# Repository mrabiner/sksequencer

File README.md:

# sksequencer
Kondo RF Sequencer

## Function
This board is a TX/RX sequencer for an amateur-radio station. An ATmega328P monitors the PTT line from the radio. When PTT is keyed (pulled to ground), the firmware switches the station in a set order: it removes power from the mast-mounted LNA, switches the coax relays and then enables the power amplifier. When PTT is released, it runs the same steps in reverse. This keeps RF out of the LNA and keeps the relays from switching while RF is present (no hot-switching). The sequence timing is set by the firmware.

## Inputs / Outputs

| Pad | Name | Type | Description |
|-----|------|------|-------------|
| TP13 | 5V PAD | Power in | +5 V logic supply. Protected by F1 (0.5 A polyfuse), Q7 (reverse-polarity P-FET) and D6 (6.8 V TVS) |
| TP15 | V1 | Power in | +15 V LNA supply, switched to the LNA output |
| TP16 | V2 | Power in | +28 V coax-relay supply, switched to the RELAY output |
| TP12 | PTT | Input | PTT from the radio, active low. 10k pull-up to +5 V, 1k series resistor and 100 nF filter cap, to PD2 |
| TP8 | LNA | Output | High-side switched +15 V (Q5 BS250P driven by Q1), with flyback diode |
| TP9 | RELAY | Output | High-side switched +28 V (Q6 BS250P driven by Q2), with flyback diode |
| TP10 | AMP | Output | Low-side open-drain output (Q3 BS170) for amplifier keying, clamped by a 36 V TVS |
| TP11 | OUT#4 | Output | Low-side open-drain output (Q4 BS170), spare, clamped by a 36 V TVS |
| TP14, TP17–TP21 | GND | Ground | Ground pads |

### Headers
| Ref | Description |
|-----|-------------|
| J1 | 1x4, output drive signals PD5, PD6, PD7, PB0 (MCU side of the gate resistors) |
| J2 | 1x6, RESET, PD0/RXD, PD1/TXD, PD2 (PTT), PD3, PD4 |
| J3 | 1x14, PC0–PC5, GND, AREF, +5 V, PB5–PB1 (spare I/O) |
| J4 | 2x3 AVR ISP programming header |
| SW1 | Reset pushbutton |

The MCU runs from a 16 MHz crystal (Y1). D1 is a +5 V power indicator LED.

## Project Files

| File | Description |
|------|-------------|
| `sequencer.kicad_pro` | KiCad project file |
| `sequencer.kicad_sch` | Schematic |
| `sequencer.kicad_pcb` | PCB layout |
| `sequencer.kicad_sym` | Project symbol library (BS250P and others) |
| `ECS-160-18-4X-CKM.kicad_sym` | Symbol for the 16 MHz crystal Y1 |
| `sym-lib-table` | Project symbol library table |
| `fp-lib-table` | Project footprint library table |
| `.gitignore` | Leaves KiCad backups, history, `.kicad_prl` user settings and generated output out of git |

**Note:** `fp-lib-table` references `sequencer footprint library.pretty` (footprints for Y1, Q5 and Q6), which is not yet in the repository.

Created with KiCad 10.

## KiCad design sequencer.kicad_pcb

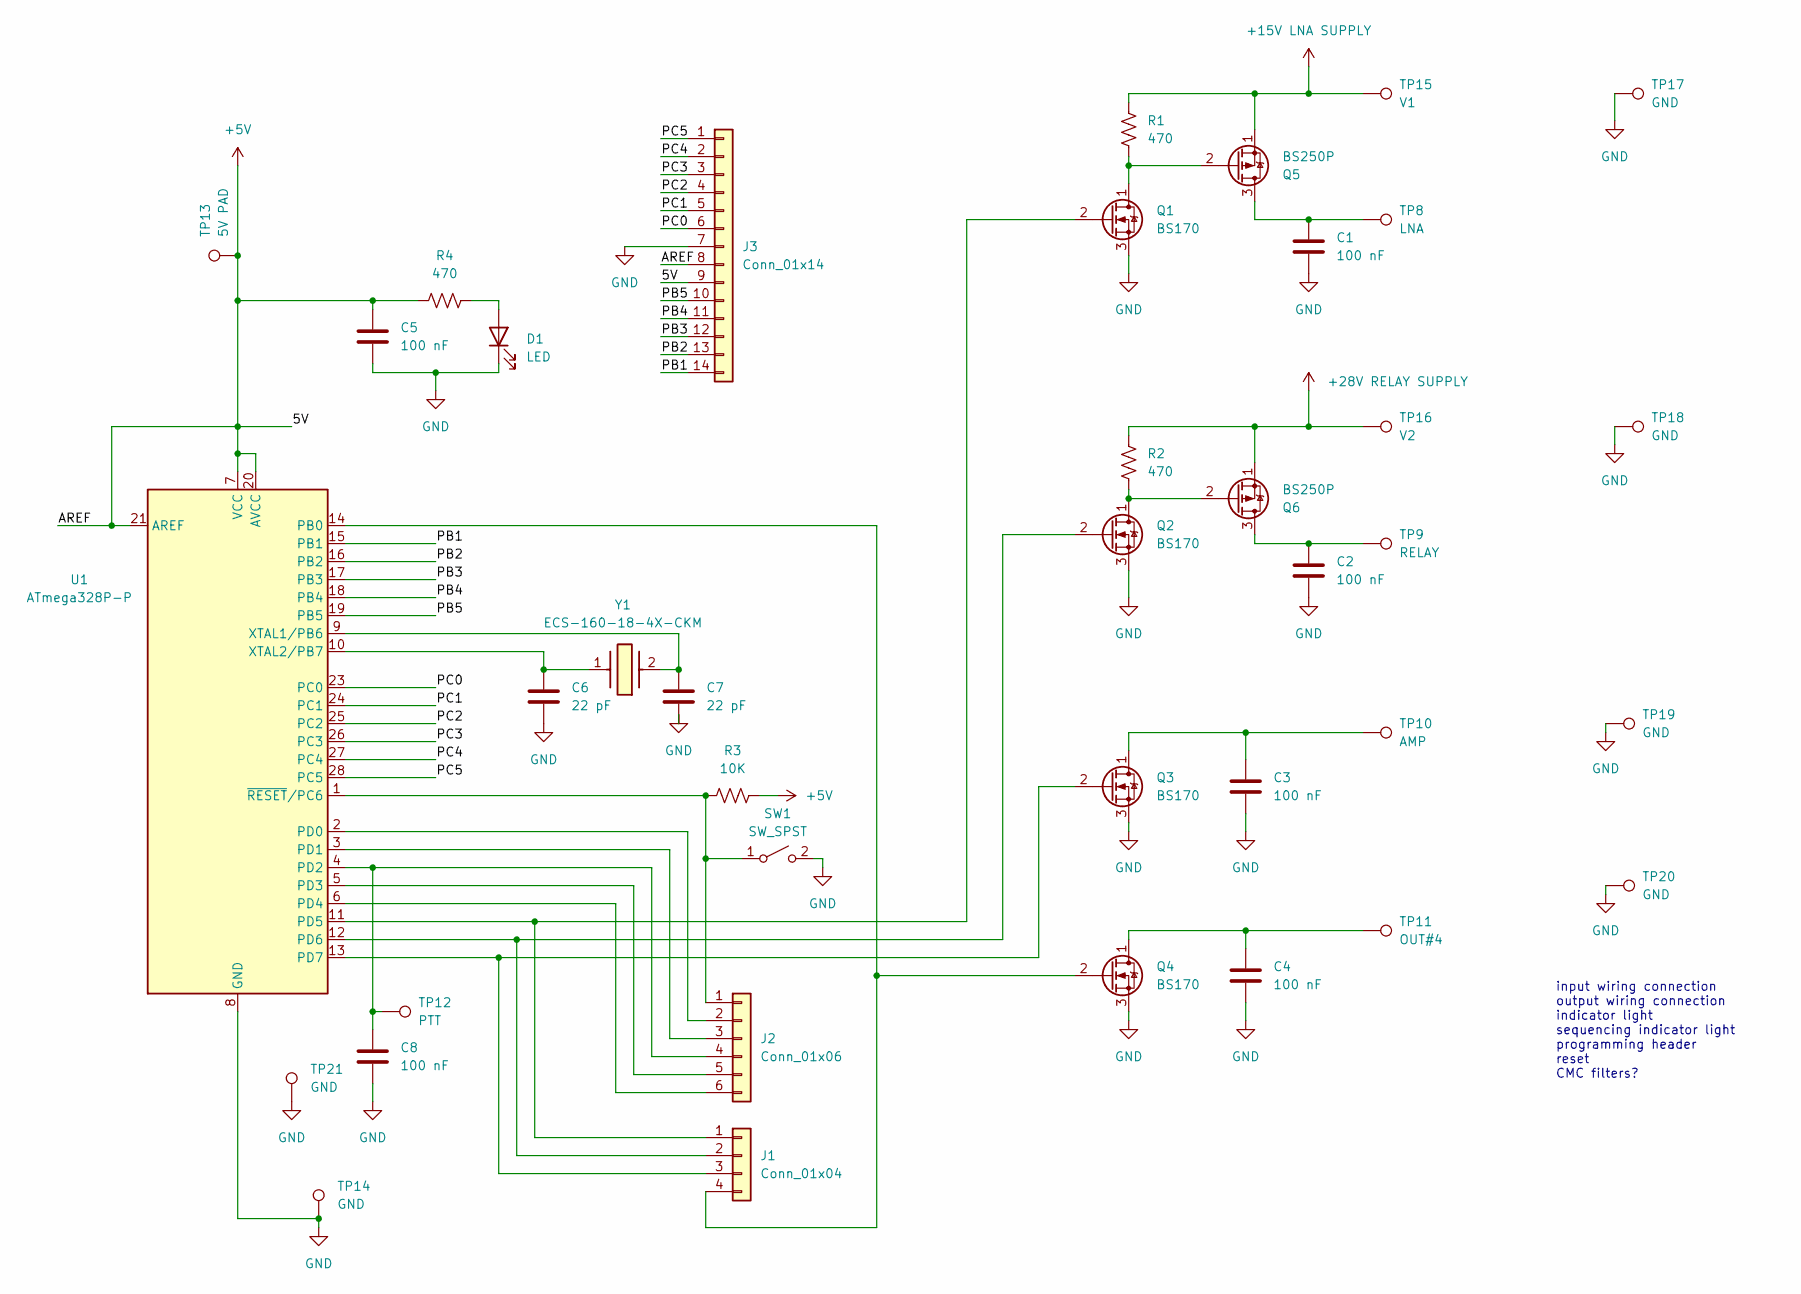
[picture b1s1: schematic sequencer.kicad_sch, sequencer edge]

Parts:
C1, C2, C3, C4, C5, C8: 100 nF; C_Disc_D3.8mm_W2.6mm_P2.50mm
C6, C7: 22 pF; C_Disc_D3.8mm_W2.6mm_P2.50mm
D1: LED; LED_D5.0mm
J1: Conn_01x04; PinSocket_1x04_P2.54mm_Vertical
J2: Conn_01x06; PinSocket_1x06_P2.54mm_Vertical
J3: Conn_01x14; PinSocket_1x14_P2.54mm_Vertical
Q1, Q2, Q3, Q4: BS170; TO-92_Inline
Q5, Q6: BS250P
R1, R2, R4: 470; R_Axial_DIN0204_L3.6mm_D1.6mm_P2.54mm_Vertical
R3: 10K; R_Axial_DIN0204_L3.6mm_D1.6mm_P2.54mm_Vertical
SW1: SW_SPST
TP8: LNA; SolderWirePad_1x01_SMD_4x8mm
TP9: RELAY; SolderWirePad_1x01_SMD_4x8mm
TP10: AMP; SolderWirePad_1x01_SMD_4x8mm
TP11: OUT#4; SolderWirePad_1x01_SMD_4x8mm
TP12: PTT; SolderWirePad_1x01_SMD_4x8mm
TP13: 5V PAD; SolderWirePad_1x01_SMD_4x8mm
TP14, TP17, TP18, TP19, TP20, TP21: GND; SolderWirePad_1x01_SMD_4x8mm
TP15: V1; SolderWirePad_1x01_SMD_4x8mm
TP16: V2; SolderWirePad_1x01_SMD_4x8mm
U1: ATmega328P-P; DIP-28_W7.62mm
Y1: ECS-160-18-4X-CKM; ECS160184XCKM; Mouser Part Number 520-ECS160-18-4X-CKM

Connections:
+5V: C5.1, J3.8, J3.9, R3.2, R4.1, TP13.1 (1_1), U1.7 (VCC), U1.20 (AVCC), U1.21 (AREF)
+15V LNA SUPPLY: Q5.1 (S), R1.1, TP15.1 (1_1)
+28V RELAY SUPPLY: Q6.1 (S), R2.1, TP16.1 (1_1)
/PB1: J3.14, U1.15 (PB1)
/PB2: J3.13, U1.16 (PB2)
/PB3: J3.12, U1.17 (PB3)
/PB4: J3.11, U1.18 (PB4)
/PB5: J3.10, U1.19 (PB5)
/PC0: J3.6, U1.23 (PC0)
/PC1: J3.5, U1.24 (PC1)
/PC2: J3.4, U1.25 (PC2)
/PC3: J3.3, U1.26 (PC3)
/PC4: J3.2, U1.27 (PC4)
/PC5: J3.1, U1.28 (PC5)
GND: C1.2, C2.2, C3.2, C4.2, C5.2, C6.2, C7.2, C8.2, D1.1 (K), J3.7, Q1.3 (S), Q2.3 (S), Q3.3 (S), Q4.3 (S), SW1.2 (B), TP14.1 (1_1), TP17.1 (1_1), TP18.1 (1_1), TP19.1 (1_1), TP20.1 (1_1), TP21.1 (1_1), U1.8 (GND), U1.22 (GND)
unnamed: D1.2 (A), R4.2
unnamed: J1.1, Q1.2 (G), U1.11 (PD5)
unnamed: J1.2, Q2.2 (G), U1.12 (PD6)
unnamed: J1.3, Q3.2 (G), U1.13 (PD7)
unnamed: J1.4, Q4.2 (G), U1.14 (PB0)
unnamed: J2.1, R3.1, SW1.1 (A), U1.1 (~RESET/PC6)
unnamed: J2.2, U1.2 (PD0)
unnamed: J2.3, U1.3 (PD1)
unnamed: C8.1, J2.4, TP12.1 (1_1), U1.4 (PD2)
unnamed: J2.5, U1.5 (PD3)
unnamed: J2.6, U1.6 (PD4)
unnamed: Q1.1 (D), Q5.2 (G), R1.2
unnamed: Q2.1 (D), Q6.2 (G), R2.2
unnamed: C3.1, Q3.1 (D), TP10.1 (1_1)
unnamed: C4.1, Q4.1 (D), TP11.1 (1_1)
unnamed: C1.1, Q5.3 (D), TP8.1 (1_1)
unnamed: C2.1, Q6.3 (D), TP9.1 (1_1)
unnamed: C7.1, U1.9 (XTAL1/PB6), Y1.2 (CRYSTAL_2)
unnamed: C6.1, U1.10 (XTAL2/PB7), Y1.1 (CRYSTAL_1)

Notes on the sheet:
input wiring connection output wiring connection indicator light sequencing indicator light programming header reset CMC filters?

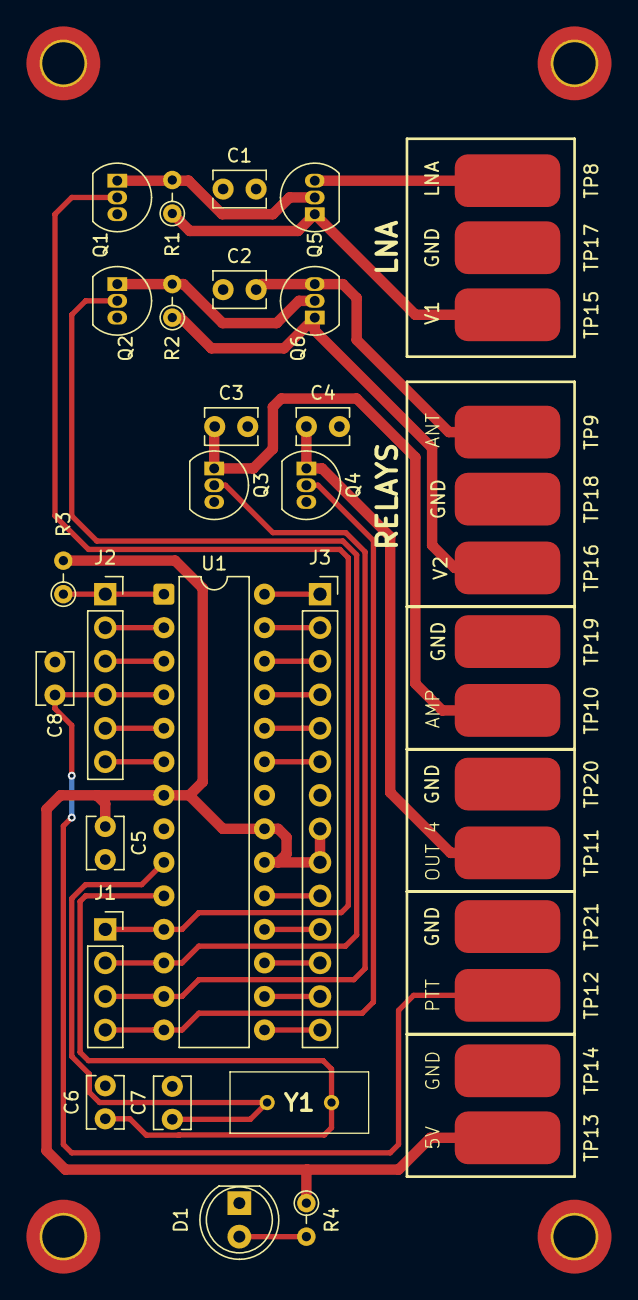
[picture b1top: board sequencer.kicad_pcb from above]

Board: 2 copper layers, 38 parts (0 on the bottom side), 34 nets.
